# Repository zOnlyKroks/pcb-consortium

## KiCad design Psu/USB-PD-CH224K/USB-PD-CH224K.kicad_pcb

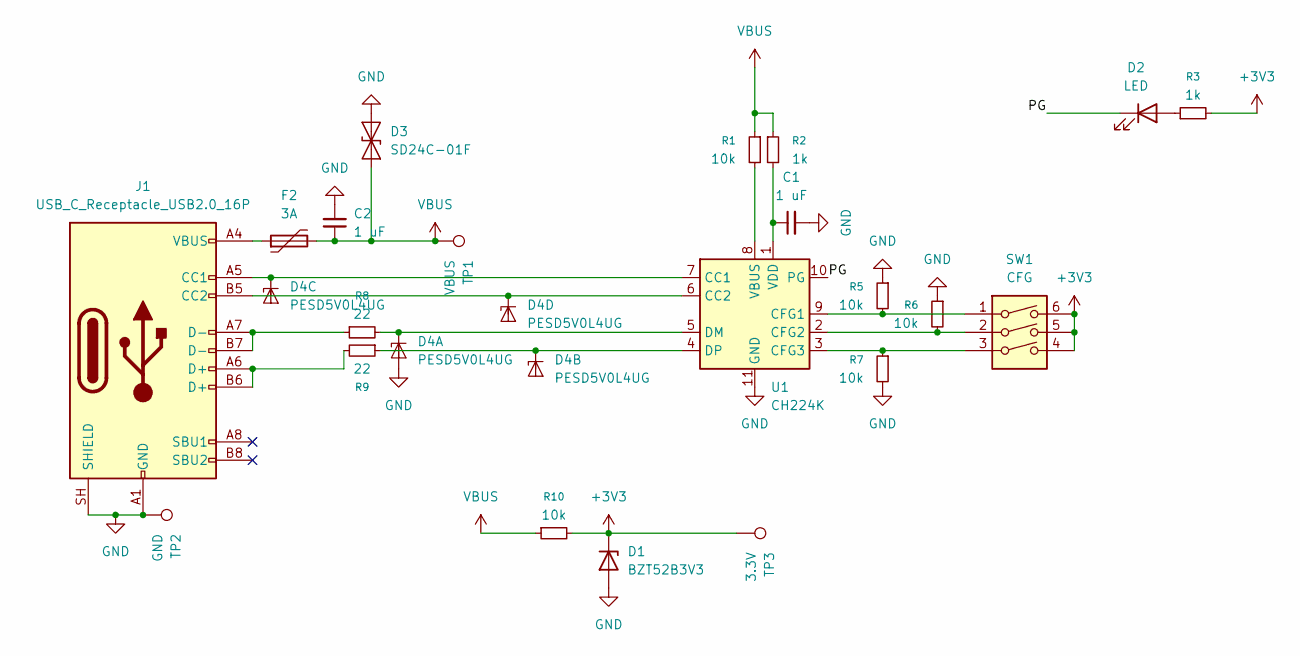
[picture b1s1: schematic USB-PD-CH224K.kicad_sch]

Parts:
C1, C2: 1 uF; C_0603_1608Metric
D1: BZT52B3V3; D_SOD-123
D2: LED; LED_0603_1608Metric
D3: SD24C-01F; D_SOD-323
D4: PESD5V0L4UG; SOT-353_SC-70-5
F2: 3A; Fuse_0603_1608Metric
J1: USB_C_Receptacle_USB2.0_16P; USB_C_Receptacle_HRO_TYPE-C-31-M-12; LCSC Part # C165948
R1, R5, R6, R7, R10: 10k; R_0603_1608Metric
R2, R3: 1k; R_0603_1608Metric
R8, R9: 22; R_0603_1608Metric
SW1: CFG; SW_DIP_SPSTx03_Slide_6.7x9.18mm_W8.61mm_P2.54mm_LowProfile; LCSC Part # C7421520
TP1: VBUS; TestPoint_Pad_1.0x1.0mm
TP2: GND; TestPoint_Pad_1.0x1.0mm
TP3: 3.3V; TestPoint_Pad_1.0x1.0mm
U1: CH224K; SSOP-10-1EP_3.9x4.9mm_P1mm_EP2.1x3.3mm

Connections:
+3V3: D1.1 (K), R3.2, R10.2, SW1.4, SW1.5, SW1.6, TP3.1 (1_1)
/PG: D2.1 (K), U1.10 (PG)
GND: C1.2, C2.2, D1.2 (A), D3.2 (A2), D4.2 (A), J1.A1 (GND), J1.A12 (GND), J1.B1 (GND), J1.B12 (GND), J1.SH (SHIELD), R5.1, R6.1, R7.2, TP2.1 (1_1), U1.11 (GND)
unnamed: D2.2 (A), R3.1
unnamed: D4.1 (K1), R8.2, U1.5 (DM)
unnamed: D4.3 (K2), R9.1, U1.4 (DP)
unnamed: D4.4 (K3), J1.A5 (CC1), U1.7 (CC1)
unnamed: D4.5 (K4), J1.B5 (CC2), U1.6 (CC2)
unnamed: F2.1, J1.A4 (VBUS), J1.A9 (VBUS), J1.B4 (VBUS), J1.B9 (VBUS)
unnamed: J1.A6 (D+), J1.B6 (D+), R9.2
unnamed: J1.A7 (D-), J1.B7 (D-), R8.1
unnamed: R5.2, SW1.1, U1.9 (CFG1)
unnamed: R6.2, SW1.2, U1.2 (CFG2)
unnamed: R7.1, SW1.3, U1.3 (CFG3)
unnamed: R1.2, U1.8 (VBUS)
unnamed: C1.1, R2.2, U1.1 (VDD)
VBUS: C2.1, D3.1 (A1), F2.2, R1.1, R2.1, R10.1, TP1.1 (1_1)

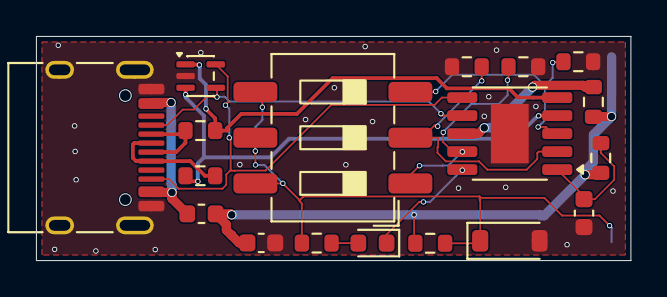
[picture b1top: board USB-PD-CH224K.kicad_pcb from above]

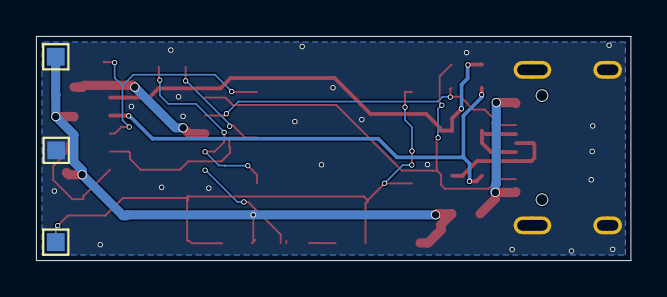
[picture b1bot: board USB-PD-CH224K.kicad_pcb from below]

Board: 2 copper layers, 33.0 x 12.5 mm, 21 parts (3 on the bottom side), 17 nets.

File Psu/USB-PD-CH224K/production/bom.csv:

Designator,Footprint,Quantity,Value,LCSC Part #
"C1, C2",0603,2,1 uF,C15849
D1,D_SOD-123,1,BZT52B3V3,C19077392
D2,0603,1,LED,C2286
D3,D_SOD-323,1,SD24C-01F,C151295
D4,SOT-353_SC-70-5,1,PESD5V0L4UG,C80694
F2,0603,1,3A,C1512048
J1,USB_C_Receptacle_HRO_TYPE-C-31-M-12,1,USB_C_Receptacle_USB2.0_16P,C165948
"R1, R10, R5, R6, R7",0603,5,10k,C25804
"R2, R3",0603,2,1k,C21190
"R8, R9",0603,2,22,C23345
SW1,SW_DIP_SPSTx03_Slide_6.7x9.18mm_W8.61mm_P2.54mm_LowProfile,1,CFG,C7421520
TP1,TestPoint_Pad_1.0x1.0mm,1,VBUS,
TP2,TestPoint_Pad_1.0x1.0mm,1,GND,
TP3,TestPoint_Pad_1.0x1.0mm,1,3.3V,
U1,SSOP-10-1EP_3.9x4.9mm_P1mm_EP2.1x3.3mm,1,CH224K,C970725

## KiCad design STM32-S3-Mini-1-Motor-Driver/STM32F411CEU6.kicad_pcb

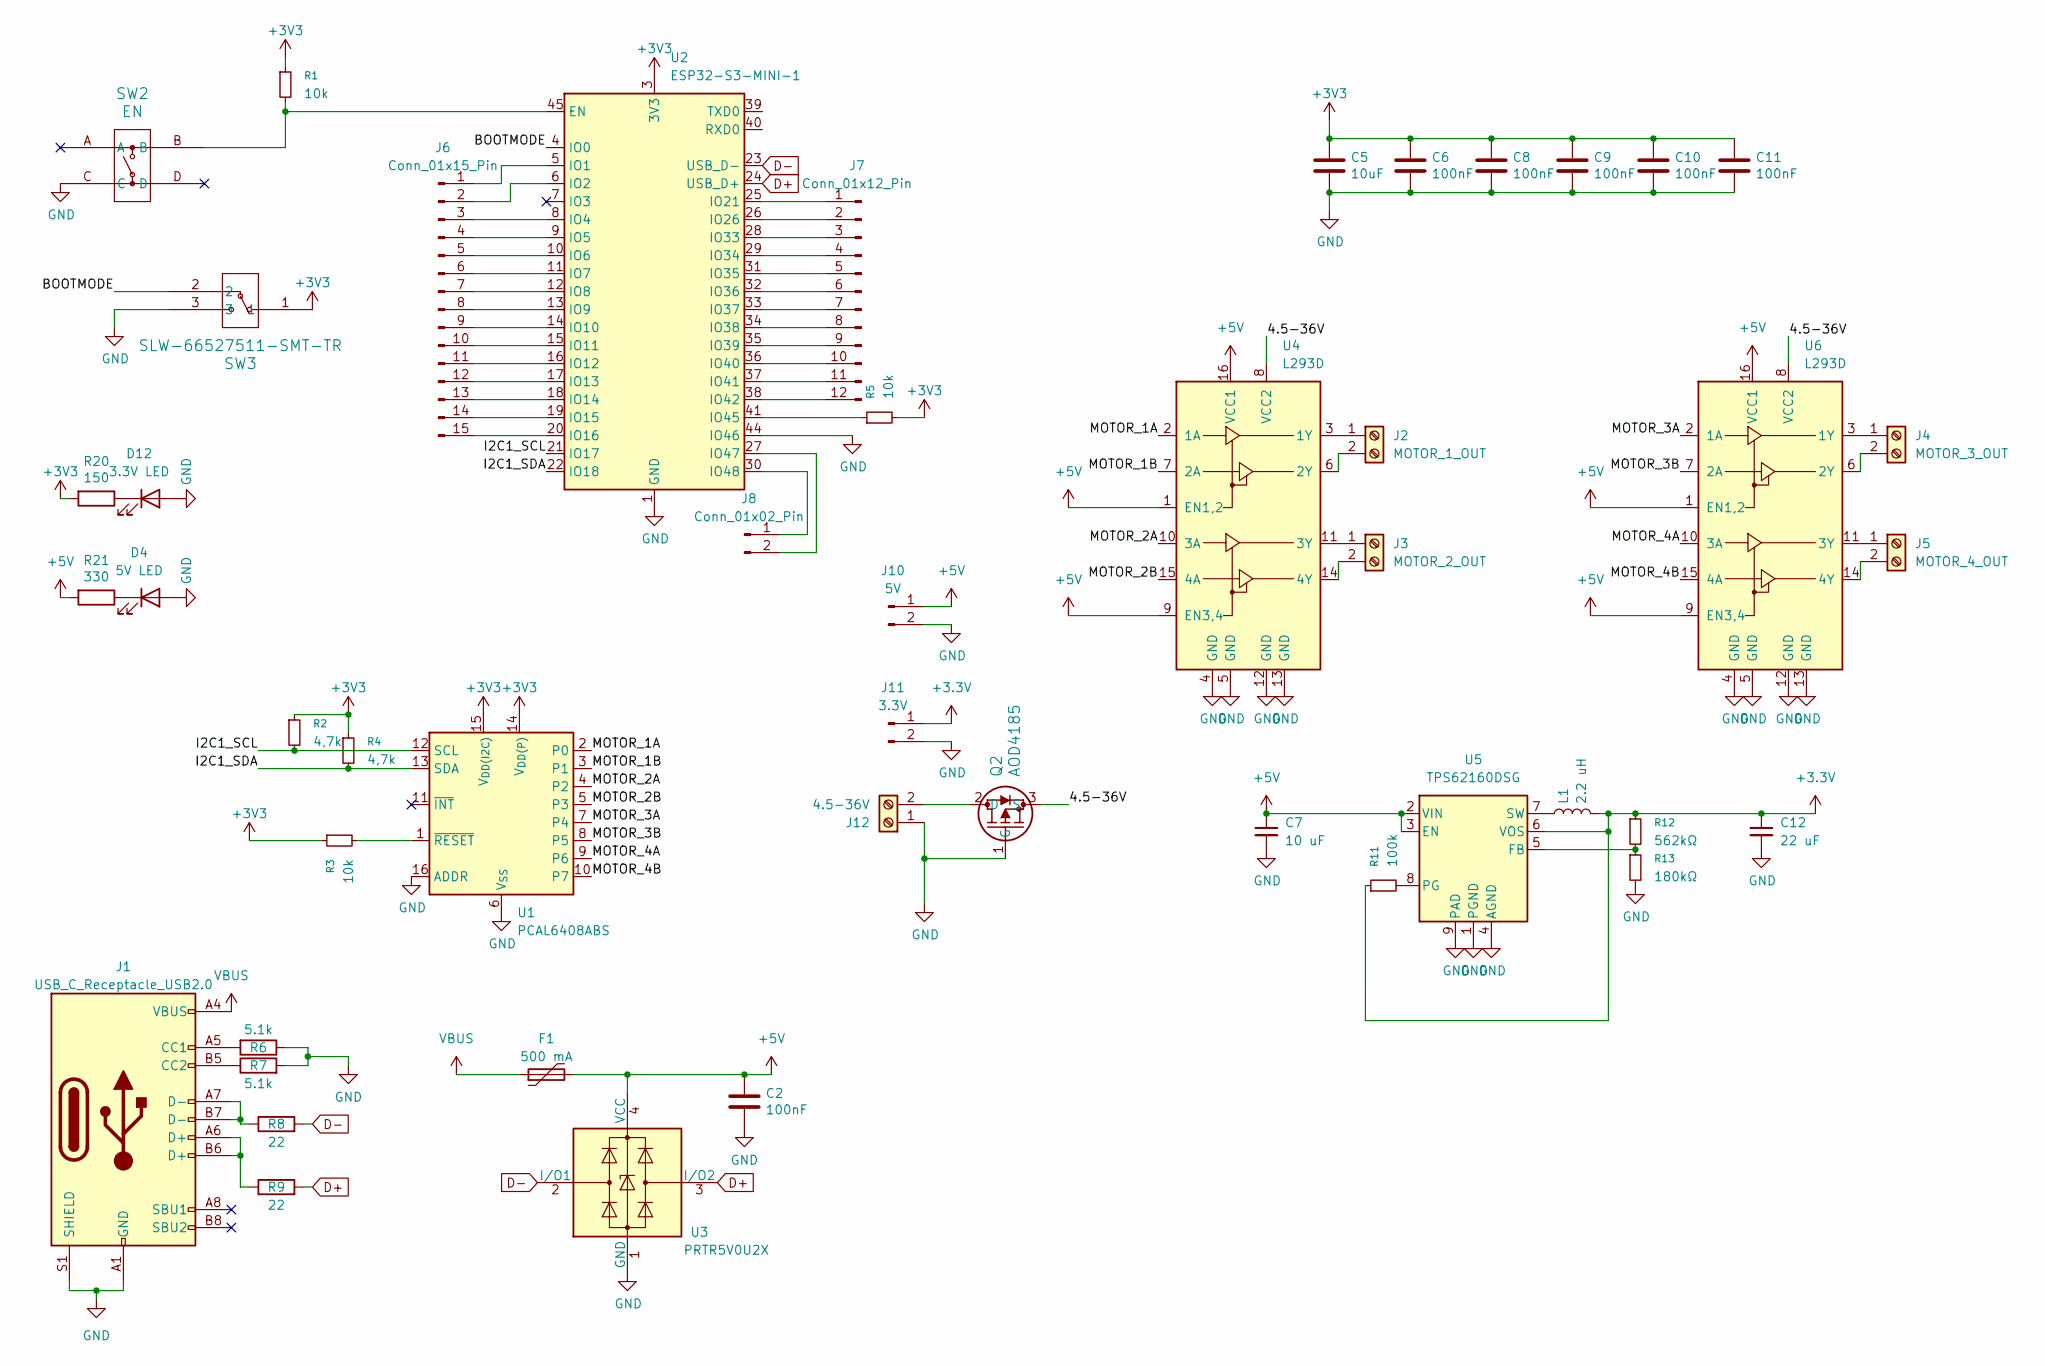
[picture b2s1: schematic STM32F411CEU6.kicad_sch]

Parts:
C2, C6, C8, C9, C10, C11: 100nF; C_0805_2012Metric; LCSC C28233
C5: 10uF; C_0805_2012Metric; LCSC C15850
C7: 10 uF; C_0805_2012Metric; LCSC Part # C15850
C12: 22 uF; C_0805_2012Metric; LCSC Part # C45783
D4: 5V LED; LED_0805_2012Metric; LCSC Part # C98225
D12: 3.3V LED; LED_0805_2012Metric; LCSC Part # C98225
F1: 500 mA; Fuse_1206_3216Metric; LCSC C135341
J1: USB_C_Receptacle_USB2.0; USB_C_Receptacle_HRO_TYPE-C-31-M-12; JlcRotOffset 180
J2: MOTOR_1_OUT; TerminalBlock_Phoenix_MKDS-1,5-2-5.08_1x02_P5.08mm_Horizont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; LCSC Part # C5183929
J3: MOTOR_2_OUT; TerminalBlock_Phoenix_MKDS-1,5-2-5.08_1x02_P5.08mm_Horizont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; LCSC Part # C5183929
J4: MOTOR_3_OUT; TerminalBlock_Phoenix_MKDS-1,5-2-5.08_1x02_P5.08mm_Horizont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; LCSC Part # C5183929
J5: MOTOR_4_OUT; TerminalBlock_Phoenix_MKDS-1,5-2-5.08_1x02_P5.08mm_Horizont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; LCSC Part # C5183929
J6: Conn_01x15_Pin; PinHeader_1x15_P2.54mm_Vertical; LCSC Part # C7501269
J7: Conn_01x12_Pin; PinHeader_1x12_P2.54mm_Vertical; LCSC Part # C2840012
J8: Conn_01x02_Pin; PinHeader_1x02_P2.54mm_Vertical; LCSC Part # C42431798
J10: 5V; PinHeader_1x02_P2.54mm_Vertical; LCSC Part # C42431798
J11: 3.3V; PinHeader_1x02_P2.54mm_Vertical; LCSC Part # C42431798
J12: 4.5-36V; TerminalBlock_Phoenix_MKDS-1,5-2-5.08_1x02_P5.08mm_Horizont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; LCSC Part # C5183929
L1: 2.2 uH; IND_PA4332.222NLT; LCSC Part # C3222957
Q2: AOD4185; TO252_AOS; LCSC Part # C400894
R1, R3, R5: 10k; R_0805_2012Metric; LCSC Part # C17414
R2, R4: 4,7k; R_0805_2012Metric; LCSC Part # C17673
R6, R7: 5.1k; R_0805_2012Metric; LCSC Part # C27834
R8, R9: 22; R_0805_2012Metric; LCSC Part # C17561
R11: 100k; R_0805_2012Metric; LCSC Part # C149504
R12: 562kΩ; R_0805_2012Metric; LCSC Part # C2849274
R13: 180kΩ; R_0805_2012Metric; LCSC Part # C17501
R20: 150; R_0805_2012Metric; LCSC Part # C17471
R21: 330; R_0805_2012Metric; LCSC Part # C17630
SW2: EN; KH-6X6X5H-STM_SKE; LCSC Part # C2837531
SW3: SLW-66527511-SMT-TR; SLW-66527511-SMT-TR_CUD
U1: PCAL6408ABS; VQFN-16-1EP_3x3mm_P0.5mm_EP1.6x1.6mm; LCSC Part # C2652332
U2: ESP32-S3-MINI-1; ESP32-S2-MINI-1; LCSC Part # C2913206
U3: PRTR5V0U2X; SOT-143; LCSC C2827688
U4, U6: L293D; DIP-16_W7.62mm; LCSC Part # C12340
U5: TPS62160DSG; WSON-8-1EP_2x2mm_P0.5mm_EP0.9x1.6mm_ThermalVias; LCSC Part # C324077

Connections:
+3.3V: C12.1, J11.1, L1.2, R11.1, R12.1, U5.6 (VOS)
+3V3: C5.1, C6.1, C8.1, C9.1, C10.1, C11.1, R1.1, R2.1, R3.1, R4.1, R5.2, R20.2, SW3.1, U1.14 (V_{DD(P)}), U1.15 (V_{DD(I2C)}), U2.3 (3V3)
+5V: C2.1, C7.1, F1.2, J10.1, R21.2, U3.4 (VCC), U4.1 (EN1,2), U4.9 (EN3,4), U4.16 (VCC1), U5.2 (VIN), U5.3 (EN), U6.1 (EN1,2), U6.9 (EN3,4), U6.16 (VCC1)
/4.5-36V: Q2.3 (S), U4.8 (VCC2), U6.8 (VCC2)
/BOOTMODE: SW3.2, U2.4 (IO0)
/I2C1_SCL: R2.2, U1.12 (SCL), U2.21 (IO17)
/I2C1_SDA: R4.2, U1.13 (SDA), U2.22 (IO18)
/MOTOR_1A: U1.2 (P0), U4.2 (1A)
/MOTOR_1B: U1.3 (P1), U4.7 (2A)
/MOTOR_2A: U1.4 (P2), U4.10 (3A)
/MOTOR_2B: U1.5 (P3), U4.15 (4A)
/MOTOR_3A: U1.7 (P4), U6.2 (1A)
/MOTOR_3B: U1.8 (P5), U6.7 (2A)
/MOTOR_4A: U1.9 (P6), U6.10 (3A)
/MOTOR_4B: U1.10 (P7), U6.15 (4A)
D+: R9.2, U2.24 (USB_D+), U3.3 (I/O2)
D-: R8.2, U2.23 (USB_D-), U3.2 (I/O1)
GND: C2.2, C5.2, C6.2, C7.2, C8.2, C9.2, C10.2, C11.2, C12.2, D4.2 (A), D12.2 (A), J1.A1 (GND), J1.A12 (GND), J1.B1 (GND), J1.B12 (GND), J1.S1 (SHIELD), J10.2, J11.2, J12.1, Q2.1 (G), R6.1, R7.2, R13.2, SW2.C, SW3.3, U1.6 (V_{SS}), U1.16 (ADDR), U1.17 (V_{SS}), U2.1 (GND), U2.2 (GND), U2.42 (GND), U2.43 (GND), U2.44 (IO46), U2.46 (GND), U2.47 (GND), U2.48 (GND), U2.49 (GND), U2.50 (GND), U2.51 (GND), U2.52 (GND), U2.53 (GND), U2.54 (GND), U2.55 (GND), U2.56 (GND), U2.57 (GND), U2.58 (GND), U2.59 (GND), U2.60 (GND), U2.61 (GND), U2.62 (GND), U2.63 (GND), U2.64 (GND), U2.65 (GND), U3.1 (GND), U4.4 (GND), U4.5 (GND), U4.12 (GND), U4.13 (GND), U5.1 (PGND), U5.4 (AGND), U5.9 (PAD), U6.4 (GND), U6.5 (GND), U6.12 (GND), U6.13 (GND)
unnamed: D4.1 (K), R21.1
unnamed: D12.1 (K), R20.1
unnamed: J1.A5 (CC1), R6.2
unnamed: J1.B5 (CC2), R7.1
unnamed: J1.A6 (D+), J1.B6 (D+), R9.1
unnamed: J1.A7 (D-), J1.B7 (D-), R8.1
unnamed: J2.1, U4.3 (1Y)
unnamed: J2.2, U4.6 (2Y)
unnamed: J3.1, U4.11 (3Y)
unnamed: J3.2, U4.14 (4Y)
unnamed: J4.1, U6.3 (1Y)
unnamed: J4.2, U6.6 (2Y)
unnamed: J5.1, U6.11 (3Y)
unnamed: J5.2, U6.14 (4Y)
unnamed: J6.1, U2.5 (IO1)
unnamed: J6.2, U2.6 (IO2)
unnamed: J6.3, U2.8 (IO4)
unnamed: J6.4, U2.9 (IO5)
unnamed: J6.5, U2.10 (IO6)
unnamed: J6.6, U2.11 (IO7)
unnamed: J6.7, U2.12 (IO8)
unnamed: J6.8, U2.13 (IO9)
unnamed: J6.9, U2.14 (IO10)
unnamed: J6.10, U2.15 (IO11)
unnamed: J6.11, U2.16 (IO12)
unnamed: J6.12, U2.17 (IO13)
unnamed: J6.13, U2.18 (IO14)
unnamed: J6.14, U2.19 (IO15)
unnamed: J6.15, U2.20 (IO16)
unnamed: J7.1, U2.25 (IO21)
unnamed: J7.2, U2.26 (IO26)
unnamed: J7.3, U2.28 (IO33)
unnamed: J7.4, U2.29 (IO34)
unnamed: J7.5, U2.31 (IO35)
unnamed: J7.6, U2.32 (IO36)
unnamed: J7.7, U2.33 (IO37)
unnamed: J7.8, U2.34 (IO38)
unnamed: J7.9, U2.35 (IO39)
unnamed: J7.10, U2.36 (IO40)
unnamed: J7.11, U2.37 (IO41)
unnamed: J7.12, U2.38 (IO42)
unnamed: J8.1, U2.30 (IO48)
unnamed: J8.2, U2.27 (IO47)
unnamed: J12.2, Q2.2 (D)
unnamed: R3.2, U1.1 (~RESET)
unnamed: R1.2, SW2.B, U2.45 (EN)
unnamed: R5.1, U2.41 (IO45)
unnamed: R12.2, R13.1, U5.5 (FB)
unnamed: R11.2, U5.8 (PG)
unnamed: L1.1, U5.7 (SW)
VBUS: F1.1, J1.A4 (VBUS), J1.A9 (VBUS), J1.B4 (VBUS), J1.B9 (VBUS)

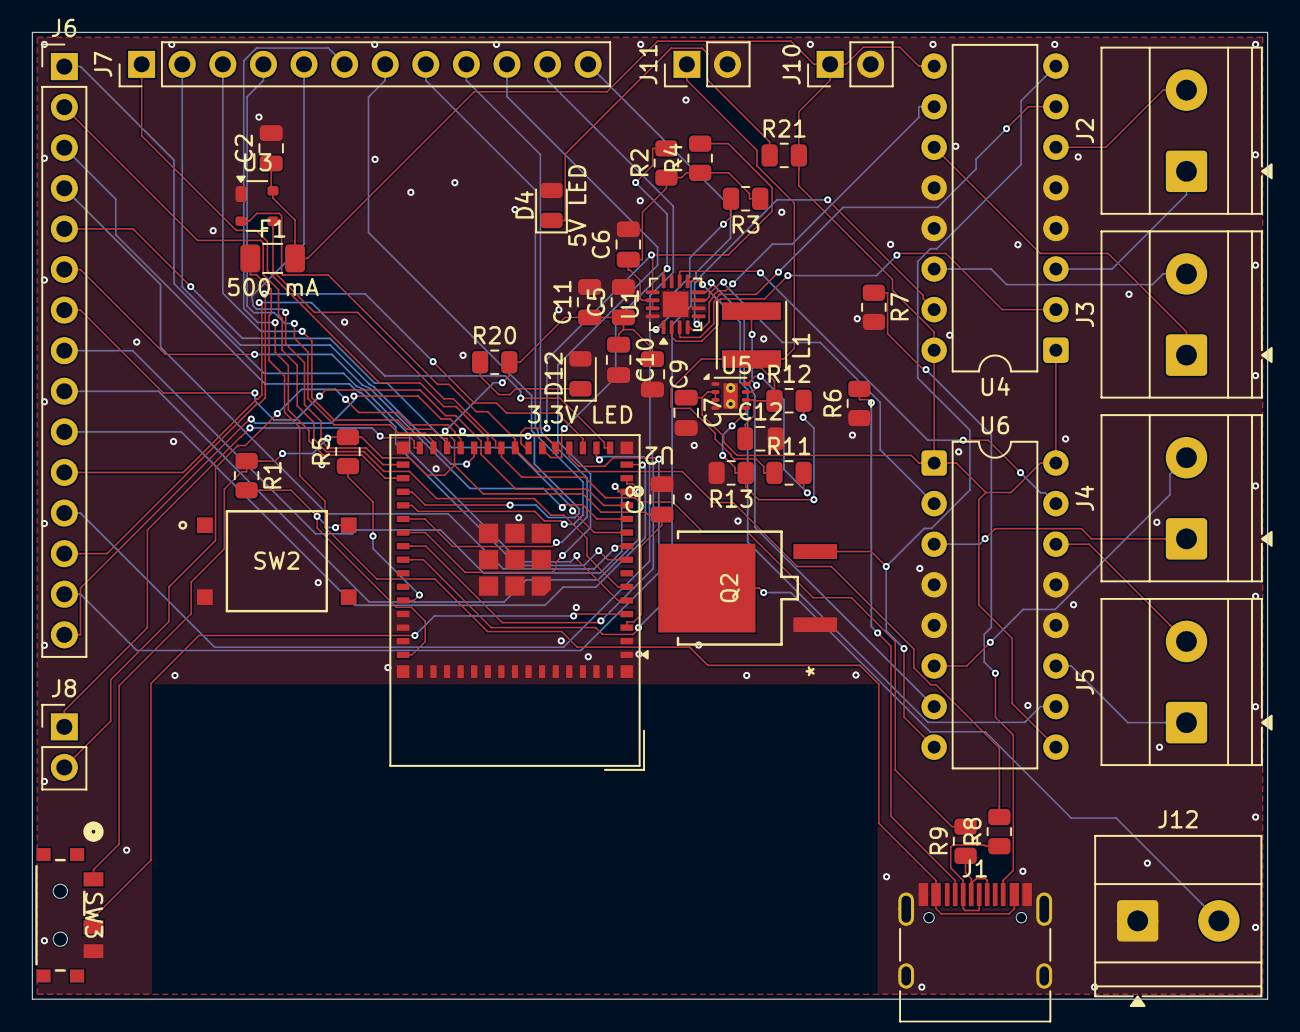
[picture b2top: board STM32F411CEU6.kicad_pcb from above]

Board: 2 copper layers, 77.3 x 60.5 mm, 47 parts (0 on the bottom side), 69 nets.

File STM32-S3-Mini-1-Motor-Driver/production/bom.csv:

Designator,Footprint,Quantity,Value,LCSC Part #
"C10, C11, C2, C6, C8, C9",0805,6,100nF,C28233
C12,0805,1,22 uF,C45783
C5,0805,1,10uF,C15850
C7,0805,1,10 uF,C15850
D12,0805,1,3.3V LED,C98225
D4,0805,1,5V LED,C98225
F1,1206,1,500 mA,C135341
J1,USB_C_Receptacle_HRO_TYPE-C-31-M-12,1,USB_C_Receptacle_USB2.0,C165948
J10,PinHeader_1x02_P2.54mm_Vertical,1,5V,C42431798
J11,PinHeader_1x02_P2.54mm_Vertical,1,3.3V,C42431798
J12,"TerminalBlock_Phoenix_MKDS-1,5-2-5.08_1x02_P5.08mm_Horizontal",1,4.5-36V,C5183929
J2,"TerminalBlock_Phoenix_MKDS-1,5-2-5.08_1x02_P5.08mm_Horizontal",1,MOTOR_1_OUT,C5183929
J3,"TerminalBlock_Phoenix_MKDS-1,5-2-5.08_1x02_P5.08mm_Horizontal",1,MOTOR_2_OUT,C5183929
J4,"TerminalBlock_Phoenix_MKDS-1,5-2-5.08_1x02_P5.08mm_Horizontal",1,MOTOR_3_OUT,C5183929
J5,"TerminalBlock_Phoenix_MKDS-1,5-2-5.08_1x02_P5.08mm_Horizontal",1,MOTOR_4_OUT,C5183929
J6,PinHeader_1x15_P2.54mm_Vertical,1,Conn_01x15_Pin,C7501269
J7,PinHeader_1x12_P2.54mm_Vertical,1,Conn_01x12_Pin,C2840012
J8,PinHeader_1x02_P2.54mm_Vertical,1,Conn_01x02_Pin,C42431798
L1,IND_PA4332.222NLT,1,2.2 uH,C3222957
Q2,TO252_AOS,1,AOD4185,C400894
"R1, R3, R5",0805,3,10k,C17414
R11,0805,1,100k,C149504
R12,0805,1,562kΩ,C2849274
R13,0805,1,180kΩ,C17501
"R2, R4",0805,2,"4,7k",C17673
R20,0805,1,150,C17471
R21,0805,1,330,C17630
"R6, R7",0805,2,5.1k,C27834
"R8, R9",0805,2,22,C17561
SW2,KH-6X6X5H-STM_SKE,1,EN,C2837531 
SW3,SLW-66527511-SMT-TR_CUD,1,SLW-66527511-SMT-TR,
U1,VQFN-16-1EP_3x3mm_P0.5mm_EP1.6x1.6mm,1,PCAL6408ABS,C2652332
U2,ESP32-S2-MINI-1,1,ESP32-S3-MINI-1,C2913206 
U3,SOT-143,1,PRTR5V0U2X,C2827688
"U4, U6",DIP-16_W7.62mm,2,L293D,C12340 
U5,WSON-8-1EP_2x2mm_P0.5mm_EP0.9x1.6mm_ThermalVias,1,TPS62160DSG,C324077

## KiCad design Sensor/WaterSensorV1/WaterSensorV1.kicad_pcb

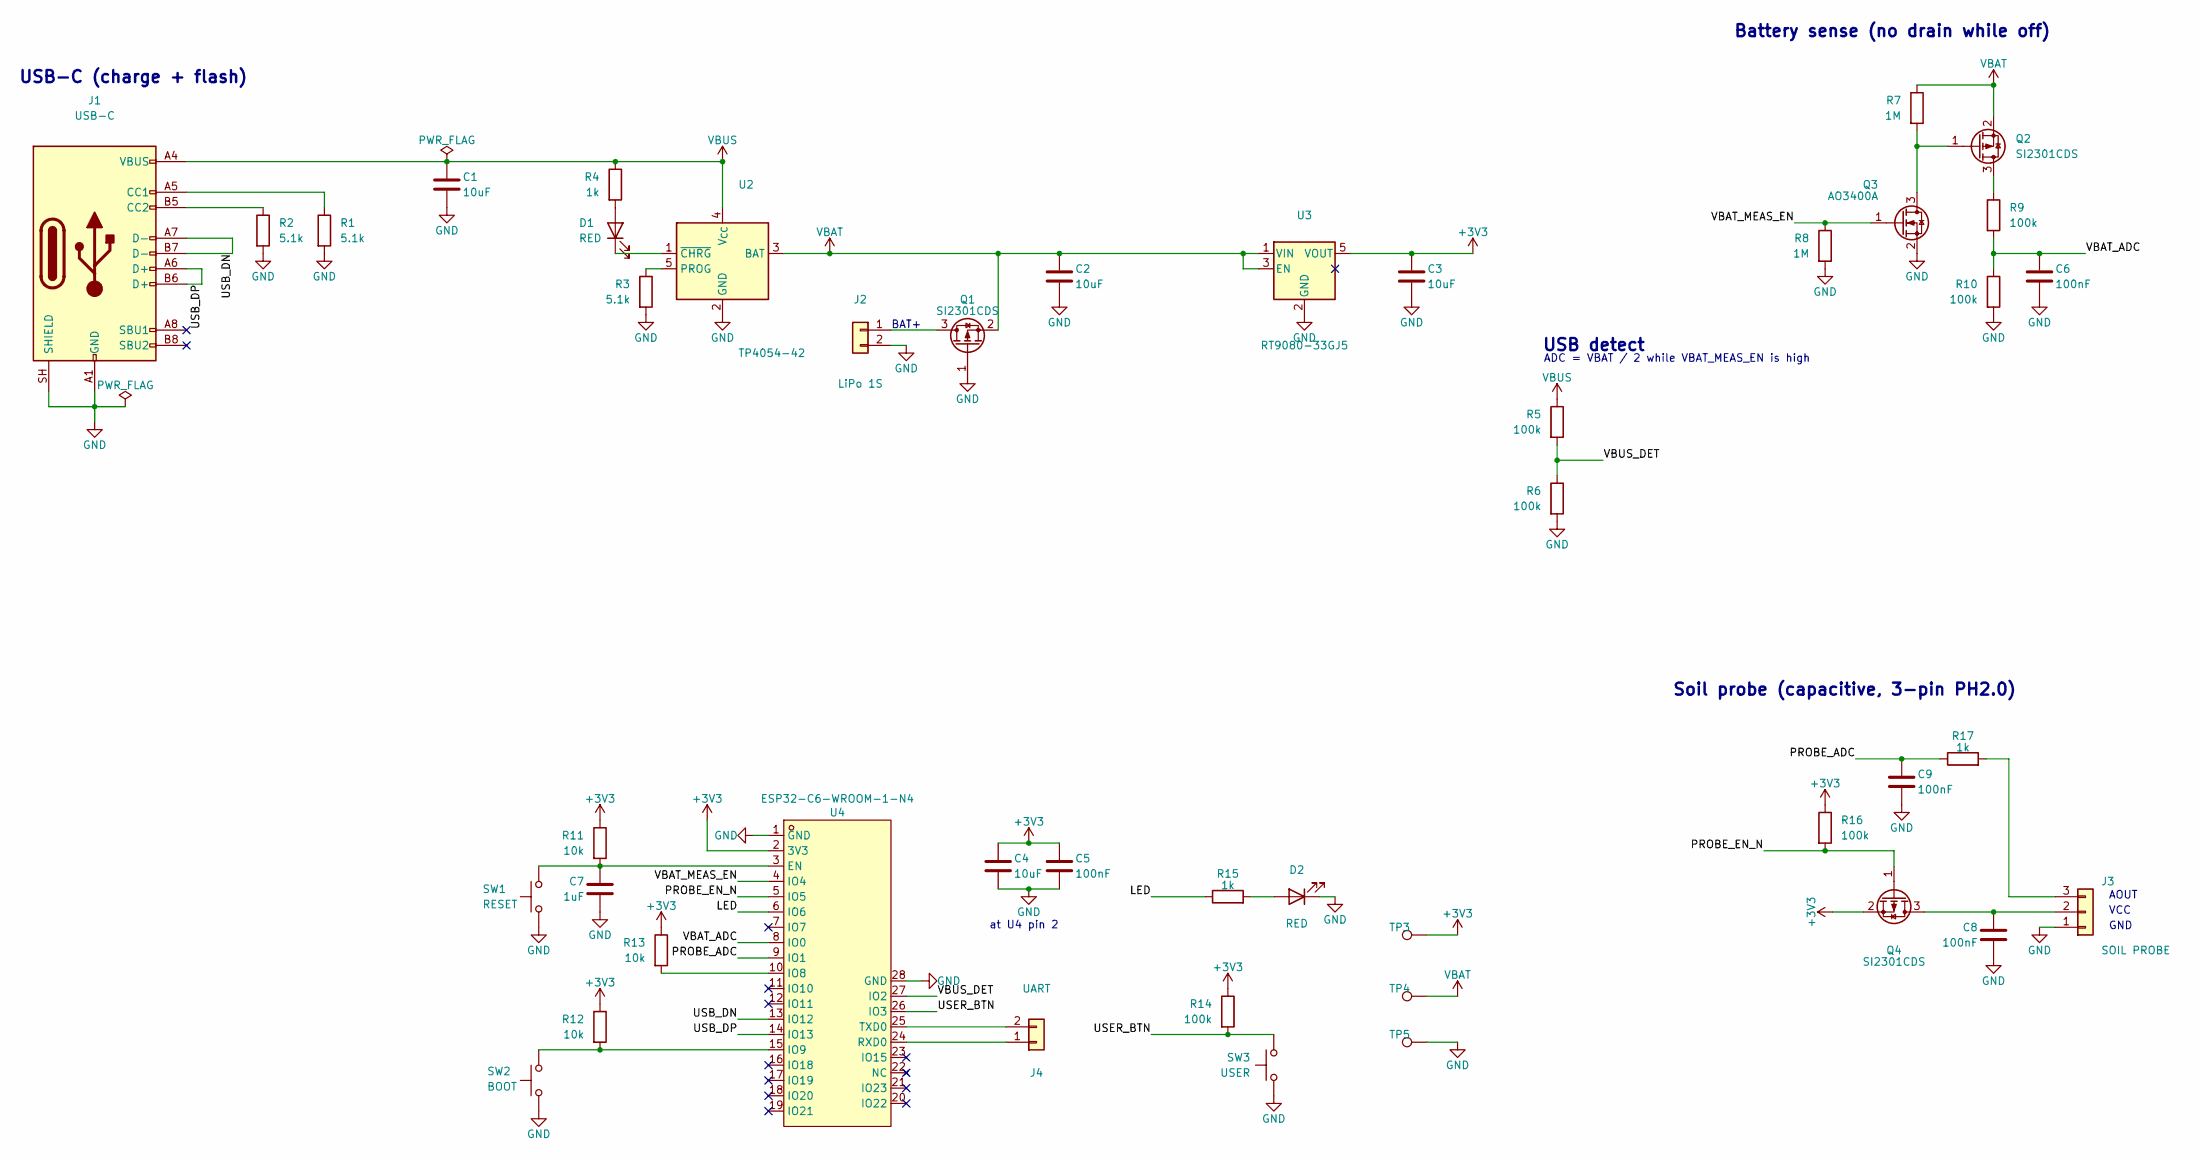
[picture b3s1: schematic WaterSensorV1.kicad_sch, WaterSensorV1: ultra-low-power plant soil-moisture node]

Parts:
C1, C2, C3, C4: 10uF; C_0603_1608Metric; LCSC Part # C19702
C5, C6, C8, C9: 100nF; C_0603_1608Metric; LCSC Part # C14663
C7: 1uF; C_0603_1608Metric; LCSC Part # C15849
D1, D2: RED; LED_0603_1608Metric; LCSC Part # C2286
J1: USB-C; USB_C_Receptacle_HRO_TYPE-C-31-M-12; LCSC Part # C165948
J2: LiPo 1S; CONN-TH_2P-P2.00_BX-PH2.0-2PWZ; LCSC Part # C18077753
J3: SOIL PROBE; CONN-TH_3P-P2.00_BX-PH2.0-3PWZ; LCSC Part # C18077754
J4: UART; CONN-TH_2P-P2.00_BX-PH2.0-2PWZ; LCSC Part # C18077753
Q1, Q2, Q4: SI2301CDS; SOT-23; LCSC Part # C10487
Q3: AO3400A; SOT-23; LCSC Part # C20917
R1, R2, R3: 5.1k; R_0603_1608Metric; LCSC Part # C23186
R4, R15, R17: 1k; R_0603_1608Metric; LCSC Part # C21190
R5, R6, R9, R10, R14, R16: 100k; R_0603_1608Metric; LCSC Part # C25803
R7, R8: 1M; R_0603_1608Metric; LCSC Part # C22935
R11, R12, R13: 10k; R_0603_1608Metric; LCSC Part # C25804
SW1: RESET; SW-SMD_4P-L5.1-W5.1-P3.70-LS6.5-TL_H1.5; LCSC Part # C318884
SW2: BOOT; SW-SMD_4P-L5.1-W5.1-P3.70-LS6.5-TL_H1.5; LCSC Part # C318884
SW3: USER; SW-SMD_4P-L5.1-W5.1-P3.70-LS6.5-TL_H1.5; LCSC Part # C318884
TP3: 3V3; TestPoint_Pad_D1.5mm
TP4: VBAT; TestPoint_Pad_D1.5mm
TP5: GND; TestPoint_Pad_D1.5mm
U2: TP4054-42; SOT-23-5; MPN TP4054-42-SOT25R (LTC4054 pinout); LCSC Part # C32574
U3: RT9080-33GJ5; SOT-23-5; MPN RT9080-33GJ5 (AP2112K pinout); LCSC Part # C841192
U4: ESP32-C6-WROOM-1-N4; ESP32-C6-WROOM-1; LCSC Part # C6034714

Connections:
+3V3: C3.1, C4.1, C5.1, Q4.2 (S), R11.1, R12.1, R13.1, R14.1, R16.1, TP3.1 (1_1), U3.5 (VOUT), U4.2 (3V3)
/LED: R15.1, U4.6 (IO6)
/PROBE_ADC: C9.1, R17.1, U4.9 (IO1)
/PROBE_EN_N: Q4.1 (G), R16.2, U4.5 (IO5)
/USB_DN: J1.A7 (D-), J1.B7 (D-), U4.13 (IO12)
/USB_DP: J1.A6 (D+), J1.B6 (D+), U4.14 (IO13)
/USER_BTN: R14.2, SW3.3 (2), SW3.4 (2), U4.26 (IO3)
/VBAT_ADC: C6.1, R9.2, R10.1, U4.8 (IO0)
/VBAT_MEAS_EN: Q3.1 (G), R8.1, U4.4 (IO4)
/VBUS_DET: R5.2, R6.1, U4.27 (IO2)
GND: C1.2, C2.2, C3.2, C4.2, C5.2, C6.2, C7.2, C8.2, C9.2, D2.1 (K), J1.A1 (GND), J1.A12 (GND), J1.B1 (GND), J1.B12 (GND), J1.SH (SHIELD), J2.2, J3.1, Q1.1 (G), Q3.2 (S), R1.2, R2.2, R3.2, R6.2, R8.2, R10.2, SW1.1, SW1.2 (1), SW2.1, SW2.2 (1), SW3.1, SW3.2 (1), TP5.1 (1_1), U2.2 (GND), U3.2 (GND), U4.1 (GND), U4.28 (GND), U4.29 (GND), U4.30 (GND), U4.31 (GND), U4.32 (GND), U4.33 (GND), U4.34 (GND), U4.35 (GND), U4.36 (GND), U4.37 (GND)
unnamed: D1.2 (A), R4.2
unnamed: D1.1 (K), U2.1 (~CHRG)
unnamed: D2.2 (A), R15.2
unnamed: J1.A5 (CC1), R1.1
unnamed: J1.B5 (CC2), R2.1
unnamed: J2.1, Q1.3 (D)
unnamed: C8.1, J3.2, Q4.3 (D)
unnamed: J3.3, R17.2
unnamed: J4.1, U4.24 (RXD0)
unnamed: J4.2, U4.25 (TXD0)
unnamed: Q2.3 (D), R9.1
unnamed: Q2.1 (G), Q3.3 (D), R7.2
unnamed: R3.1, U2.5 (PROG)
unnamed: C7.1, R11.2, SW1.3 (2), SW1.4 (2), U4.3 (EN)
unnamed: R13.2, U4.10 (IO8)
unnamed: R12.2, SW2.3 (2), SW2.4 (2), U4.15 (IO9)
VBAT: C2.1, Q1.2 (S), Q2.2 (S), R7.1, TP4.1 (1_1), U2.3 (BAT), U3.1 (VIN), U3.3 (EN)
VBUS: C1.1, J1.A4 (VBUS), J1.A9 (VBUS), J1.B4 (VBUS), J1.B9 (VBUS), R4.1, R5.1, U2.4 (V_{CC})

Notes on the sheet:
VCC
AOUT
BAT+
GND
Battery sense (no drain while off)
at U4 pin 2
USB-C (charge + flash)
USB detect
Soil probe (capacitive, 3-pin PH2.0)
ADC = VBAT / 2 while VBAT_MEAS_EN is high

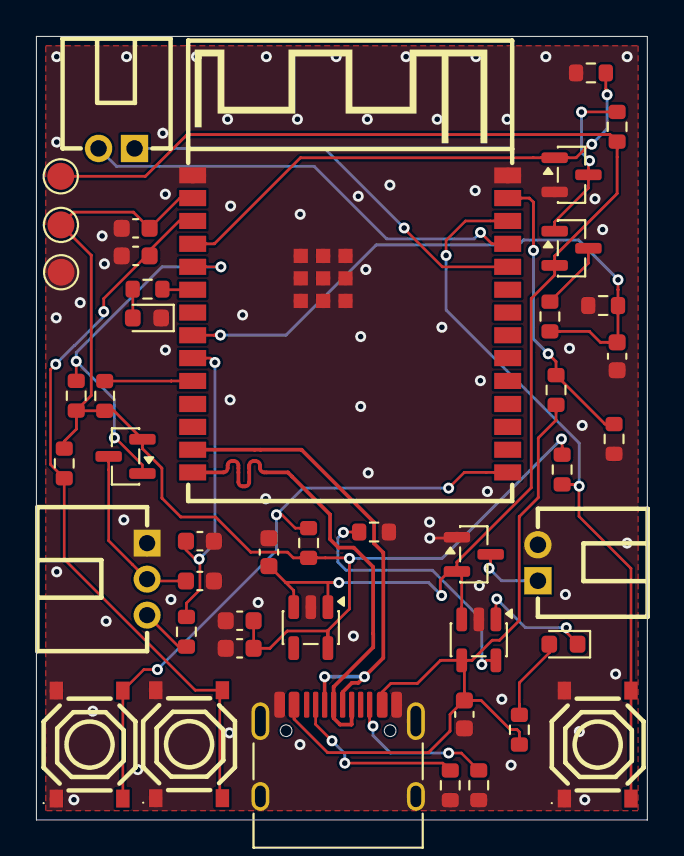
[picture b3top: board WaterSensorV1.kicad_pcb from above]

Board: 2 copper layers, 33.9 x 43.5 mm, 45 parts (0 on the bottom side), 29 nets.

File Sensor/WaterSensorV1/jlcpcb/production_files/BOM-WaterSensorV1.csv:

Comment,Designator,Footprint,LCSC,Quantity
100k,"R10,R14,R16,R5,R6,R9",R_0603_1608Metric,C25803,6
100nF,"C5,C6,C8,C9",C_0603_1608Metric,C14663,4
10k,"R11,R12,R13",R_0603_1608Metric,C25804,3
10uF,"C1,C2,C3,C4",C_0603_1608Metric,C19702,4
1M,"R7,R8",R_0603_1608Metric,C22935,2
1k,"R15,R17,R4",R_0603_1608Metric,C21190,3
1uF,C7,C_0603_1608Metric,C15849,1
5.1k,"R1,R2,R3",R_0603_1608Metric,C23186,3
AO3400A,Q3,SOT-23,C20917,1
BOOT,SW2,SW-SMD_4P-L5.1-W5.1-P3.70-LS6.5-TL_H1.5,C318884,1
ESP32-C6-WROOM-1-N4,U4,ESP32-C6-WROOM-1,C6034714,1
LiPo 1S,J2,CONN-TH_2P-P2.00_BX-PH2.0-2PWZ,C18077753,1
RED,"D1,D2",LED_0603_1608Metric,C2286,2
RESET,SW1,SW-SMD_4P-L5.1-W5.1-P3.70-LS6.5-TL_H1.5,C318884,1
RT9080-33GJ5,U3,SOT-23-5,C841192,1
SI2301CDS,"Q1,Q2,Q4",SOT-23,C10487,3
SOIL PROBE,J3,CONN-TH_3P-P2.00_BX-PH2.0-3PWZ,C18077754,1
TP4054-42,U2,SOT-23-5,C32574,1
UART,J4,CONN-TH_2P-P2.00_BX-PH2.0-2PWZ,C18077753,1
USB-C,J1,USB_C_Receptacle_HRO_TYPE-C-31-M-12,C165948,1
USER,SW3,SW-SMD_4P-L5.1-W5.1-P3.70-LS6.5-TL_H1.5,C318884,1
3V3,TP3,TestPoint_Pad_D1.5mm,,1
GND,TP5,TestPoint_Pad_D1.5mm,,1
VBAT,TP4,TestPoint_Pad_D1.5mm,,1

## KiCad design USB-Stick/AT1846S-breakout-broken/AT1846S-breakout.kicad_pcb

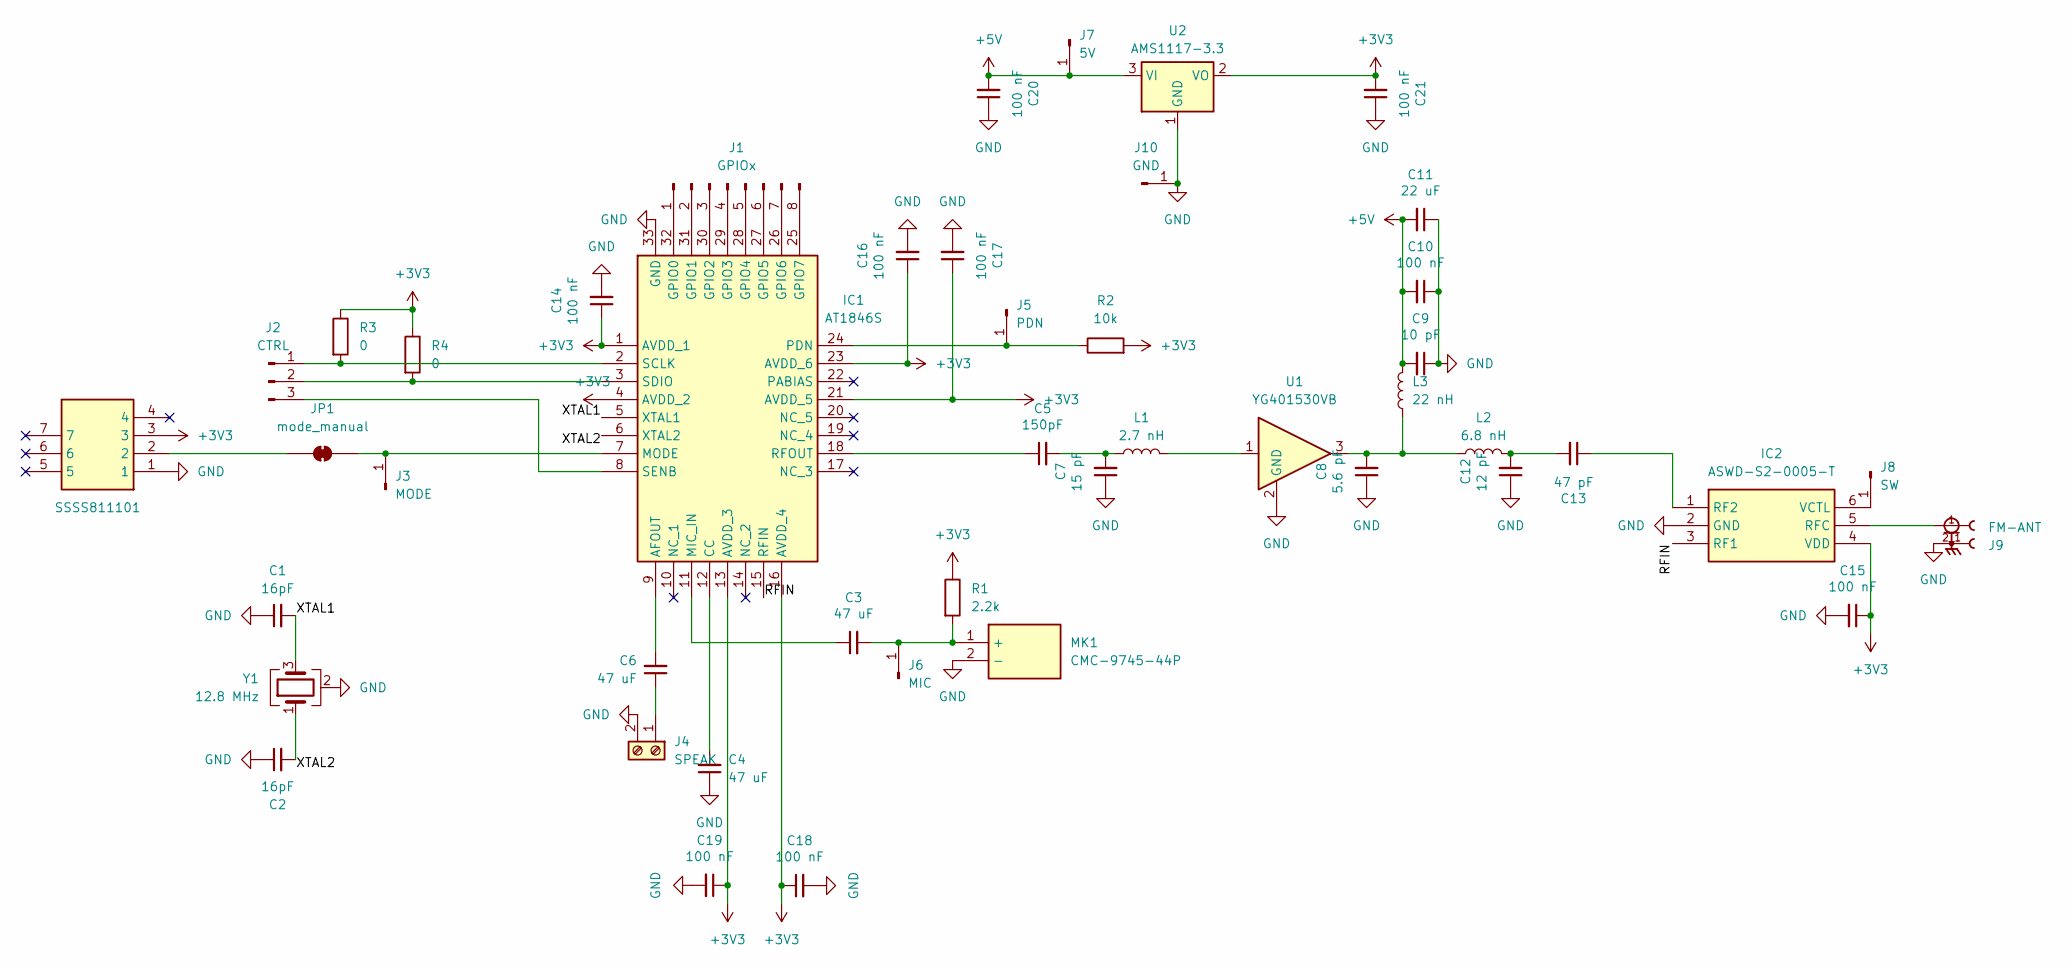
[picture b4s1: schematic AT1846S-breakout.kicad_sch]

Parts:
C1, C2: 16pF; C_0603_1608Metric
C3, C4, C6: 47 uF; C_0603_1608Metric
C5: 150pF; C_0603_1608Metric
C7: 15 pF; C_0603_1608Metric
C8: 5.6 pF; C_0603_1608Metric
C9: 10 pF; C_0603_1608Metric
C10, C14, C15, C16, C17, C18, C19, C20, C21: 100 nF; C_0603_1608Metric
C11: 22 uF; C_0603_1608Metric
C12: 12 pF; C_0603_1608Metric
C13: 47 pF; C_0603_1608Metric
IC1: AT1846S; QFN50P500X500X100-33N-D; Manufacturer_Part_Number AT1846S
IC2: ASWD-S2-0005-T; ASWDS20005T; Manufacturer_Part_Number ASWD-S2-0005-T
J1: GPIOx; PinHeader_1x08_P2.54mm_Vertical
J2: CTRL; PinHeader_1x03_P2.54mm_Vertical
J3: MODE; PinHeader_1x01_P2.54mm_Vertical
J4: SPEAK; WJ500V-5.08-2P
J5: PDN; PinHeader_1x01_P2.54mm_Vertical
J6: MIC; PinHeader_1x01_P2.54mm_Vertical
J7: 5V; PinHeader_1x01_P2.54mm_Vertical
J8: SW; PinHeader_1x01_P2.54mm_Vertical
J9: FM-ANT; BAT_WIRELESS_BWSMA-KE-Z001; PARTREV 27/12/22; LCSC Part # C496549
J10: GND; PinHeader_1x01_P2.54mm_Vertical
JP1: mode_manual; SolderJumper-2_P1.3mm_Bridged_Pad1.0x1.5mm
L1: 2.7 nH; L_0805_2012Metric
L2: 6.8 nH; L_0805_2012Metric
L3: 22 nH; L_0805_2012Metric
MK1: CMC-9745-44P; CMC974544P; Mouser Part Number 490-CMC-9745-44P
R1: 2.2k; R_0603_1608Metric
R2: 10k; R_0603_1608Metric
R3, R4: 0; R_0603_1608Metric
S1: SSSS811101; Mouser Part Number 688-SSSS811101
U1: YG401530VB; SOT-89-3
U2: AMS1117-3.3; SOT-223-3_TabPin2
Y1: 12.8 MHz; Crystal_SMD_3225-4Pin_3.2x2.5mm

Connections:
+3V3: C14.1, C15.1, C16.1, C17.1, C18.1, C19.1, C21.2, IC1.1 (AVDD_1), IC1.4 (AVDD_2), IC1.13 (AVDD_3), IC1.16 (AVDD_4), IC1.21 (AVDD_5), IC1.23 (AVDD_6), IC2.4 (VDD), R1.1, R2.2, R3.1, R4.1, S1.3, U2.2 (VO)
+5V: C9.2, C10.2, C11.2, C20.2, J7.1 (Pin_1_1), L3.2, U2.3 (VI)
/RFIN: IC1.15 (RFIN), IC2.3 (RF1)
/XTAL1: C1.2, IC1.5 (XTAL1), Y1.3
/XTAL2: C2.2, IC1.6 (XTAL2), Y1.1
GND: C1.1, C2.1, C4.1, C7.1, C8.1, C9.1, C10.1, C11.1, C12.1, C14.2, C15.2, C16.2, C17.2, C18.2, C19.2, C20.1, C21.1, IC1.33 (GND), IC2.2 (GND), J4.2, J9.2_1, J9.2_2, J9.2_3, J9.2_4, J10.1 (Pin_1_1), MK1.2 (-), S1.1, U1.2 (GND_2), U2.1 (GND), Y1.2 (G), Y1.4 (G)
unnamed: C5.2, C7.2, L1.1
unnamed: C8.2, L2.1, L3.1, U1.3
unnamed: C12.2, C13.2, L2.2
unnamed: C6.2, IC1.9 (AFOUT)
unnamed: C4.2, IC1.12 (CC)
unnamed: IC1.32 (GPIO0), J1.1
unnamed: IC1.31 (GPIO1), J1.2
unnamed: IC1.30 (GPIO2), J1.3
unnamed: IC1.29 (GPIO3), J1.4
unnamed: IC1.28 (GPIO4), J1.5
unnamed: IC1.27 (GPIO5), J1.6
unnamed: IC1.26 (GPIO6), J1.7
unnamed: IC1.25 (GPIO7), J1.8
unnamed: C3.1, IC1.11 (MIC_IN)
unnamed: IC1.7 (MODE), J3.1 (Pin_1_1), JP1.2 (B)
unnamed: IC1.24 (PDN), J5.1 (Pin_1_1), R2.1
unnamed: C5.1, IC1.18 (RFOUT)
unnamed: IC1.2 (SCLK), J2.1, R3.2
unnamed: IC1.3 (SDIO), J2.2, R4.2
unnamed: IC1.8 (SENB), J2.3
unnamed: C13.1, IC2.1 (RF2)
unnamed: IC2.5 (RFC), J9.1
unnamed: IC2.6 (VCTL), J8.1 (Pin_1_1)
unnamed: C6.1, J4.1
unnamed: C3.2, J6.1 (Pin_1_1), MK1.1 (+), R1.2
unnamed: JP1.1 (A), S1.2
unnamed: L1.2, U1.1

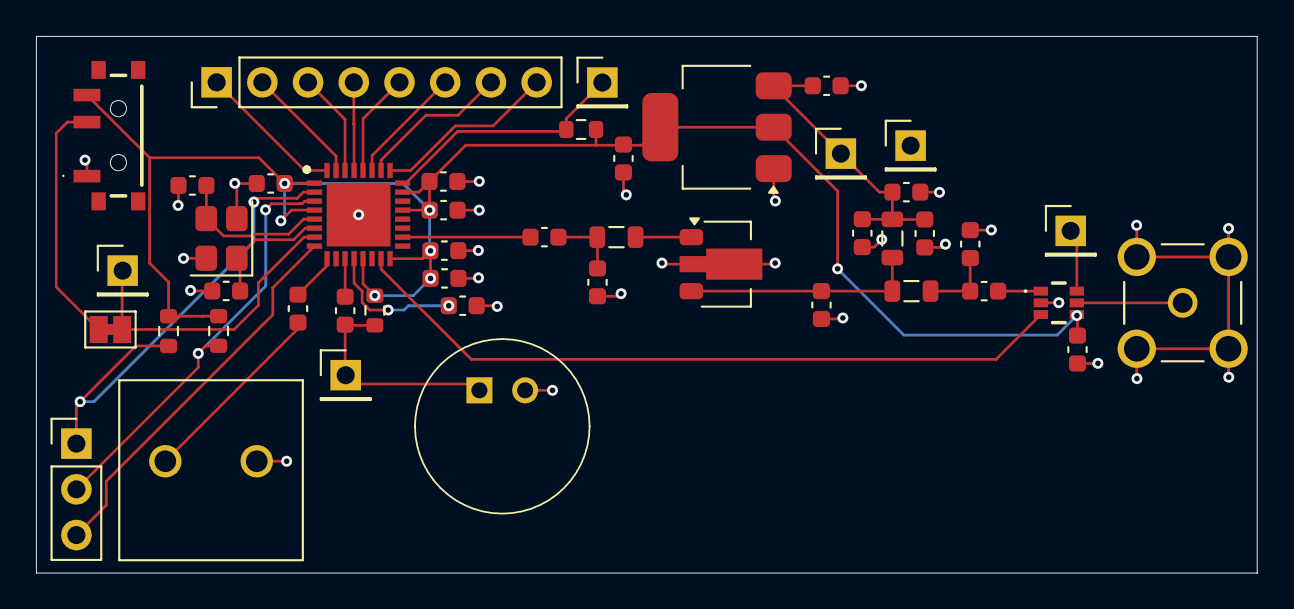
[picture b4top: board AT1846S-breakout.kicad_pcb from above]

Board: 4 copper layers, 67.8 x 29.8 mm, 46 parts (0 on the bottom side), 33 nets.
